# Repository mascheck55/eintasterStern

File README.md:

## GNU GPL V3

Copyright (c) 2026 Andreas Mascheck

# Weihnachtsstern – intelligente Lichtsteuerung mit ATtiny412

Eine stromsparende Lichtsteuerung für einen beleuchteten Weihnachtsstern. Die Steuerung verwendet einen **ATtiny412**, einen Lichtsensor und eine PWM-gesteuerte MOSFET-Endstufe.

Das Besondere: Der Stern orientiert sich am natürlichen Tagesrhythmus. Er schaltet sich bei Einbruch der Dunkelheit automatisch ein und bleibt für eine definierte Zeit eingeschaltet. Anschließend geht der Controller in einen extrem stromsparenden Tiefschlaf.

## Funktionen

- Automatisches Einschalten bei Einbruch der Dunkelheit
- Lichtmessung über einen analogen Sensor
- Einstellbare LED-Helligkeit mit vier PWM-Stufen
- Speicherung der gewählten Helligkeit im EEPROM
- Manuelle Steuerung über einen einzigen Taster
- Automatischer Tagesrhythmus ohne Echtzeituhr
- Extrem niedriger Stromverbrauch im Tiefschlaf

## Betriebsablauf

Der Controller arbeitet mit einem Zustandsautomaten:

1. **LANGSCHLAF:** 16 Stunden Tiefschlaf.
2. **WARTEN:** Regelmäßige Lichtmessung, bis die Umgebungshelligkeit unter den eingestellten Schwellwert fällt.
3. **ANZEIGE:** Beleuchtung für 5 Stunden.
4. Anschließend beginnt der Zyklus erneut mit 16 Stunden Tiefschlaf.

Die Zeitbasis liefert der interne Ultra-Low-Power-Oszillator des ATtiny412 über den RTC Periodic Interrupt Timer (PIT).

Die Beleuchtung wird somit nicht über eine feste Uhrzeit, sondern über die tatsächlichen Lichtverhältnisse gesteuert.

## Hardware

| Bauteil | Funktion | ATtiny412 |
|---|---|---|
| ATtiny412 | Mikrocontroller | – |
| MOSFET | LED-Leistungssteuerung | PA2 |
| Lichtsensor | Helligkeitsmessung | PA1 |
| Sensorversorgung | Spannungsteiler schalten | PA7 |
| Taster | Bedienung und Zustandswechsel | PA6 |

Die LED-Beleuchtung wird über einen MOSFET mit PWM angesteuert.

Die Sensorversorgung wird nur während der Messung eingeschaltet. Dadurch wird unnötiger Stromverbrauch vermieden.

## Bedienung

Der gesamte Betrieb wird mit einem einzigen Taster gesteuert.

**Kurzer Tastendruck:**

- Während der Anzeige: Beleuchtung ausschalten und in den Langschlaf wechseln.
- Im Langschlaf: Messphase starten.
- Während der Wartephase: Beleuchtung manuell einschalten.

**Langer Tastendruck (2 Sekunden) während der Anzeige:**

Aktiviert die Helligkeitseinstellung.

Jeder weitere Tastendruck schaltet zur nächsten der vier Helligkeitsstufen.

Wird der Taster 16 Sekunden lang nicht betätigt, wird die eingestellte Helligkeit im EEPROM gespeichert und der normale Betrieb fortgesetzt.

## Energiesparen

Ein Schwerpunkt des Projekts ist die Minimierung des Ruhestroms.

Dazu werden folgende Maßnahmen verwendet:

- POWER-DOWN-Schlafmodus des ATtiny412
- Abschaltung des Brown-out-Detectors während des Schlafs
- Abschaltung des ADC außerhalb der Messung
- Abschaltung des Analogkomparators
- Deaktivierung nicht benötigter digitaler Eingangspuffer
- Hochohmige Schaltung der nicht benötigten Pins im Schlafzustand
- Abschaltung der Sensorversorgung außerhalb der Messung

Der angestrebte Ruhestrom der Schaltung liegt unter 5 µA.

## Software

Die Software wurde mit **PlatformIO** und dem Arduino-Framework auf Basis von **megaTinyCore (Spence Konde)** entwickelt.

### Entwicklungsumgebung

- Mikrocontroller: ATtiny412
- Framework: Arduino
- Core: megaTinyCore
- CPU-Takt: 1 MHz
- Programmierschnittstelle: UPDI
- Upload-Protokoll: jtag2updi

### Projekt kompilieren und flashen

Repository klonen:

```bash
git clone https://github.com/mascheck55/eintasterStern.git
```

Projekt in PlatformIO öffnen und die Umgebung `Upload_UPDI` auswählen.

Die UPDI-Schnittstelle muss unter dem in `platformio.ini` eingetragenen Port erreichbar sein.

## Projektstruktur

| Verzeichnis / Datei | Inhalt |
|---|---|
| `src/` | Hauptprogramm |
| `include/` | Header-Dateien |
| `lib/` | Projektbibliotheken |
| `documents/` | Dokumentation |
| `kicad/` | Schaltungsunterlagen |
| `3Dprint/` | 3D-Druckdateien |
| `test/` | Testprogramme |
| `platformio.ini` | PlatformIO-Konfiguration |

## Hinweise

Die Schaltung ist für den Betrieb mit einer LED-Beleuchtung über MOSFET ausgelegt.

Die verwendeten PWM-Stufen und der Lichtsensor-Schwellwert können im Quellcode an die jeweilige Hardware angepasst werden.

**Hinweis:** Die Zeitsteuerung verwendet den internen Oszillator des ATtiny412. Die tatsächlichen Zeitintervalle können daher abhängig von Bauteiltoleranzen und Temperatur von den programmierten Werten abweichen.

## Lizenz

## GNU GPL V3

Copyright (c) 2026 Andreas Mascheck

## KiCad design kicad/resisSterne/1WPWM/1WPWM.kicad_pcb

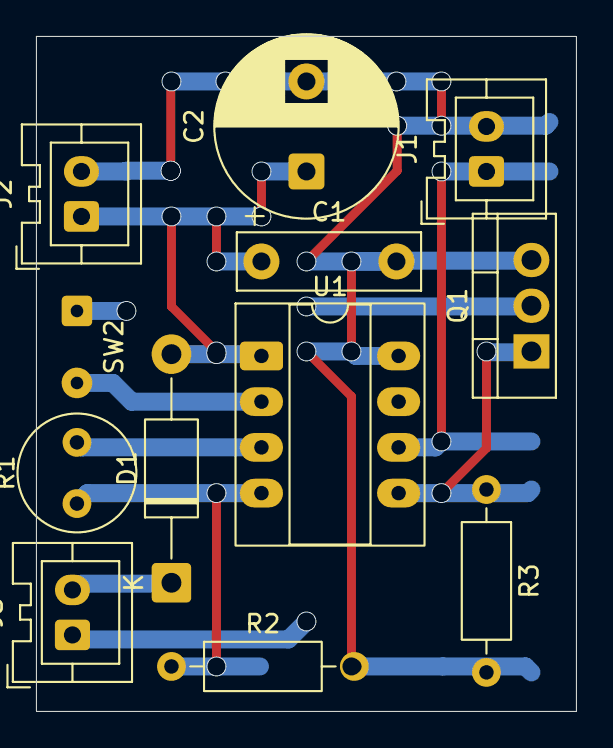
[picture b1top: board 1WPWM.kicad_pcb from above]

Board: 4 copper layers, 30.0 x 37.5 mm, 12 parts (0 on the bottom side), 9 nets.

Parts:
C1: 10n; C_Rect_L10.0mm_W3.0mm_P7.50mm_FKS3_FKP3
C2: 100uF; CP_Radial_D10.0mm_P5.00mm
D1: BA157; D_DO-41_SOD81_P12.70mm_Horizontal
J1, J2, J3: Conn_01x02_Pin; JST_XA_B02B-XASK-1_1x02_P2.50mm_Vertical
Q1: IRLZ44N; TO-220-3_Vertical
R1: A1050; R_LDR_D6.4mm_P3.4mm_Vertical
R2: 10k; R_Axial_DIN0207_L6.3mm_D2.5mm_P10.16mm_Horizontal
R3: 1k; R_Axial_DIN0207_L6.3mm_D2.5mm_P10.16mm_Horizontal
SW2: on | timer | off; SolderWire-0.15sqmm_1x02_P4mm_D0.5mm_OD1.5mm
U1: ATtiny412; CERDIP-8_W7.62mm_SideBrazed_LongPads_Socket

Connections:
GND: C1.2, C2.2, J1.2, J2.2, Q1.3 (S), R2.2, R3.2, SW2.1, U1.8 (GND)
LDR1: R1.2, U1.3 (PA7)
LDR2: R1.1, R2.1, U1.4 (PA1)
unnamed: D1.1 (K), J3.2
unnamed: J1.1, U1.6 (~RESET/PA0)
unnamed: J3.1, Q1.2 (D)
unnamed: Q1.1 (G), R3.1, U1.5 (PA2)
SW1: SW2.2, U1.2 (PA6)
VCC 5V 1A: C1.1, C2.1, D1.2 (A), J2.1, U1.1 (VCC)

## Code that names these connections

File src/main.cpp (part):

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//  sobald es dunkel wird, geht das Licht an. Die Wartephase ist unbegrenzt,
//  es wird in festem Raster gemessen, bis die Schwelle unterschritten ist.
//
//  DerZyklus lässt sich auch mit dem Tater an PA6 durchlaufen. 
//  Wird dieser Taster im Anzeigemodus mehr als eine Sekunde gedrückt, 
//  dann lässt sich die Helligkeit einstellen. Nach 16 Sekunden Untätigkeit 
//  wird dieser Wert im Flash Speicher dauerhaft gespeichert.
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
Bemerkung zu ATTINY412 in der Arduino Umgebung
In diesem Fall wird analogRead und Write verwendet - die Arduino Umgebung
hat einen Fehler beim ATTINY412 beim Pin Mapping. analogWrite auf PA3 und PA7
funktionieren deshalb nicht, PA6 wird zum wakeup interrupt gebraucht, PA1 ist
für analog read reserviert und PA0 ist ausschließlich Reset und Programming.
Deshalb ist einzig und allein PA2 für analogWrite nutzbar.
SpenceKonde November 2026 - es gibt einen Workaround ist hier aber nicht
nötig

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// ---------------------------------------------------------------------
//  PINS
// ---------------------------------------------------------------------
const uint8_t FET_PIN = PIN_PA2;        // MOSFET-Gate (PWM-Ausgang)
const uint8_t SENSOR_IN = PIN_PA1;      // ADC-Eingang Phototransistor
const uint8_t SENSOR_VCC = PIN_PA7;     // Spannungsteiler einschalten
const uint8_t TASTER_ZUSTAND = PIN_PA6; // Betriebszustand umschalten
// PIN_A3 ist unbenutzt

// Pins, die im Schlaf nie als Ausgang gefuehrt werden (hochohmig).
const uint8_t HOCHZ_PINS[] = {PIN_PA1, PIN_PA2, PIN_PA3, PIN_PA7};

// ---------------------------------------------------------------------
//  Zustandsautomat
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  bodImSchlafAusschalten();

  // Comparator bleibt dauerhaft aus (45-92 uA). Die Lichtmessung
  // erfolgt ueber den ADC an PA7/PA1.
  Comparator0.stop();

  // Taster: Pull-up, Interrupt bei fallender Flanke (Taster gegen GND)
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
// ---------------------------------------------------------------------
//  Lichtmessung
//  Phototransistor an PA1, Spannungsteiler ueber PA7 (HIGH).
//  PA1 wird als ADC-Eingang gelesen. Ergebnis < HMIN => dunkel.
// ---------------------------------------------------------------------
static bool lichtmessen()
{
  // PA1 als Ausgang kurz auf LOW (Entladen/Reset des Teilers)
  pinMode(SENSOR_IN, OUTPUT);
  digitalWrite(SENSOR_IN, LOW);
  delayMicroseconds(20);

  // PA1 wieder hochohmig
  pinMode(SENSOR_IN, INPUT);

  // PA7 als Ausgang HIGH: Spannungsteiler einschalten
  pinMode(SENSOR_VCC, OUTPUT);
  digitalWrite(SENSOR_VCC, HIGH);

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
  const bool below_threshold = (sensorValue < HMIN);

  // PA7 wieder hochohmig
  pinMode(SENSOR_VCC, INPUT);
  digitalWrite(SENSOR_VCC, LOW);

  // PA1 wieder hochohmig
  pinMode(SENSOR_IN, INPUT);
  digitalWrite(SENSOR_IN, LOW);

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  delay(1000);
}

// Entprellter Taster PA6: Zustandswechsel des Automaten.
// ---------------------------------------------------------------------
//  PA6: Zustandssteuerung und Helligkeitseinstellung
// ---------------------------------------------------------------------
static void taste6Bearbeiten()
{
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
